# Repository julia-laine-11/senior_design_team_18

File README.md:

# senior_design_team_18

See our teams progress at https://eceseniordesign.com/teams/18?semester=Fall2025

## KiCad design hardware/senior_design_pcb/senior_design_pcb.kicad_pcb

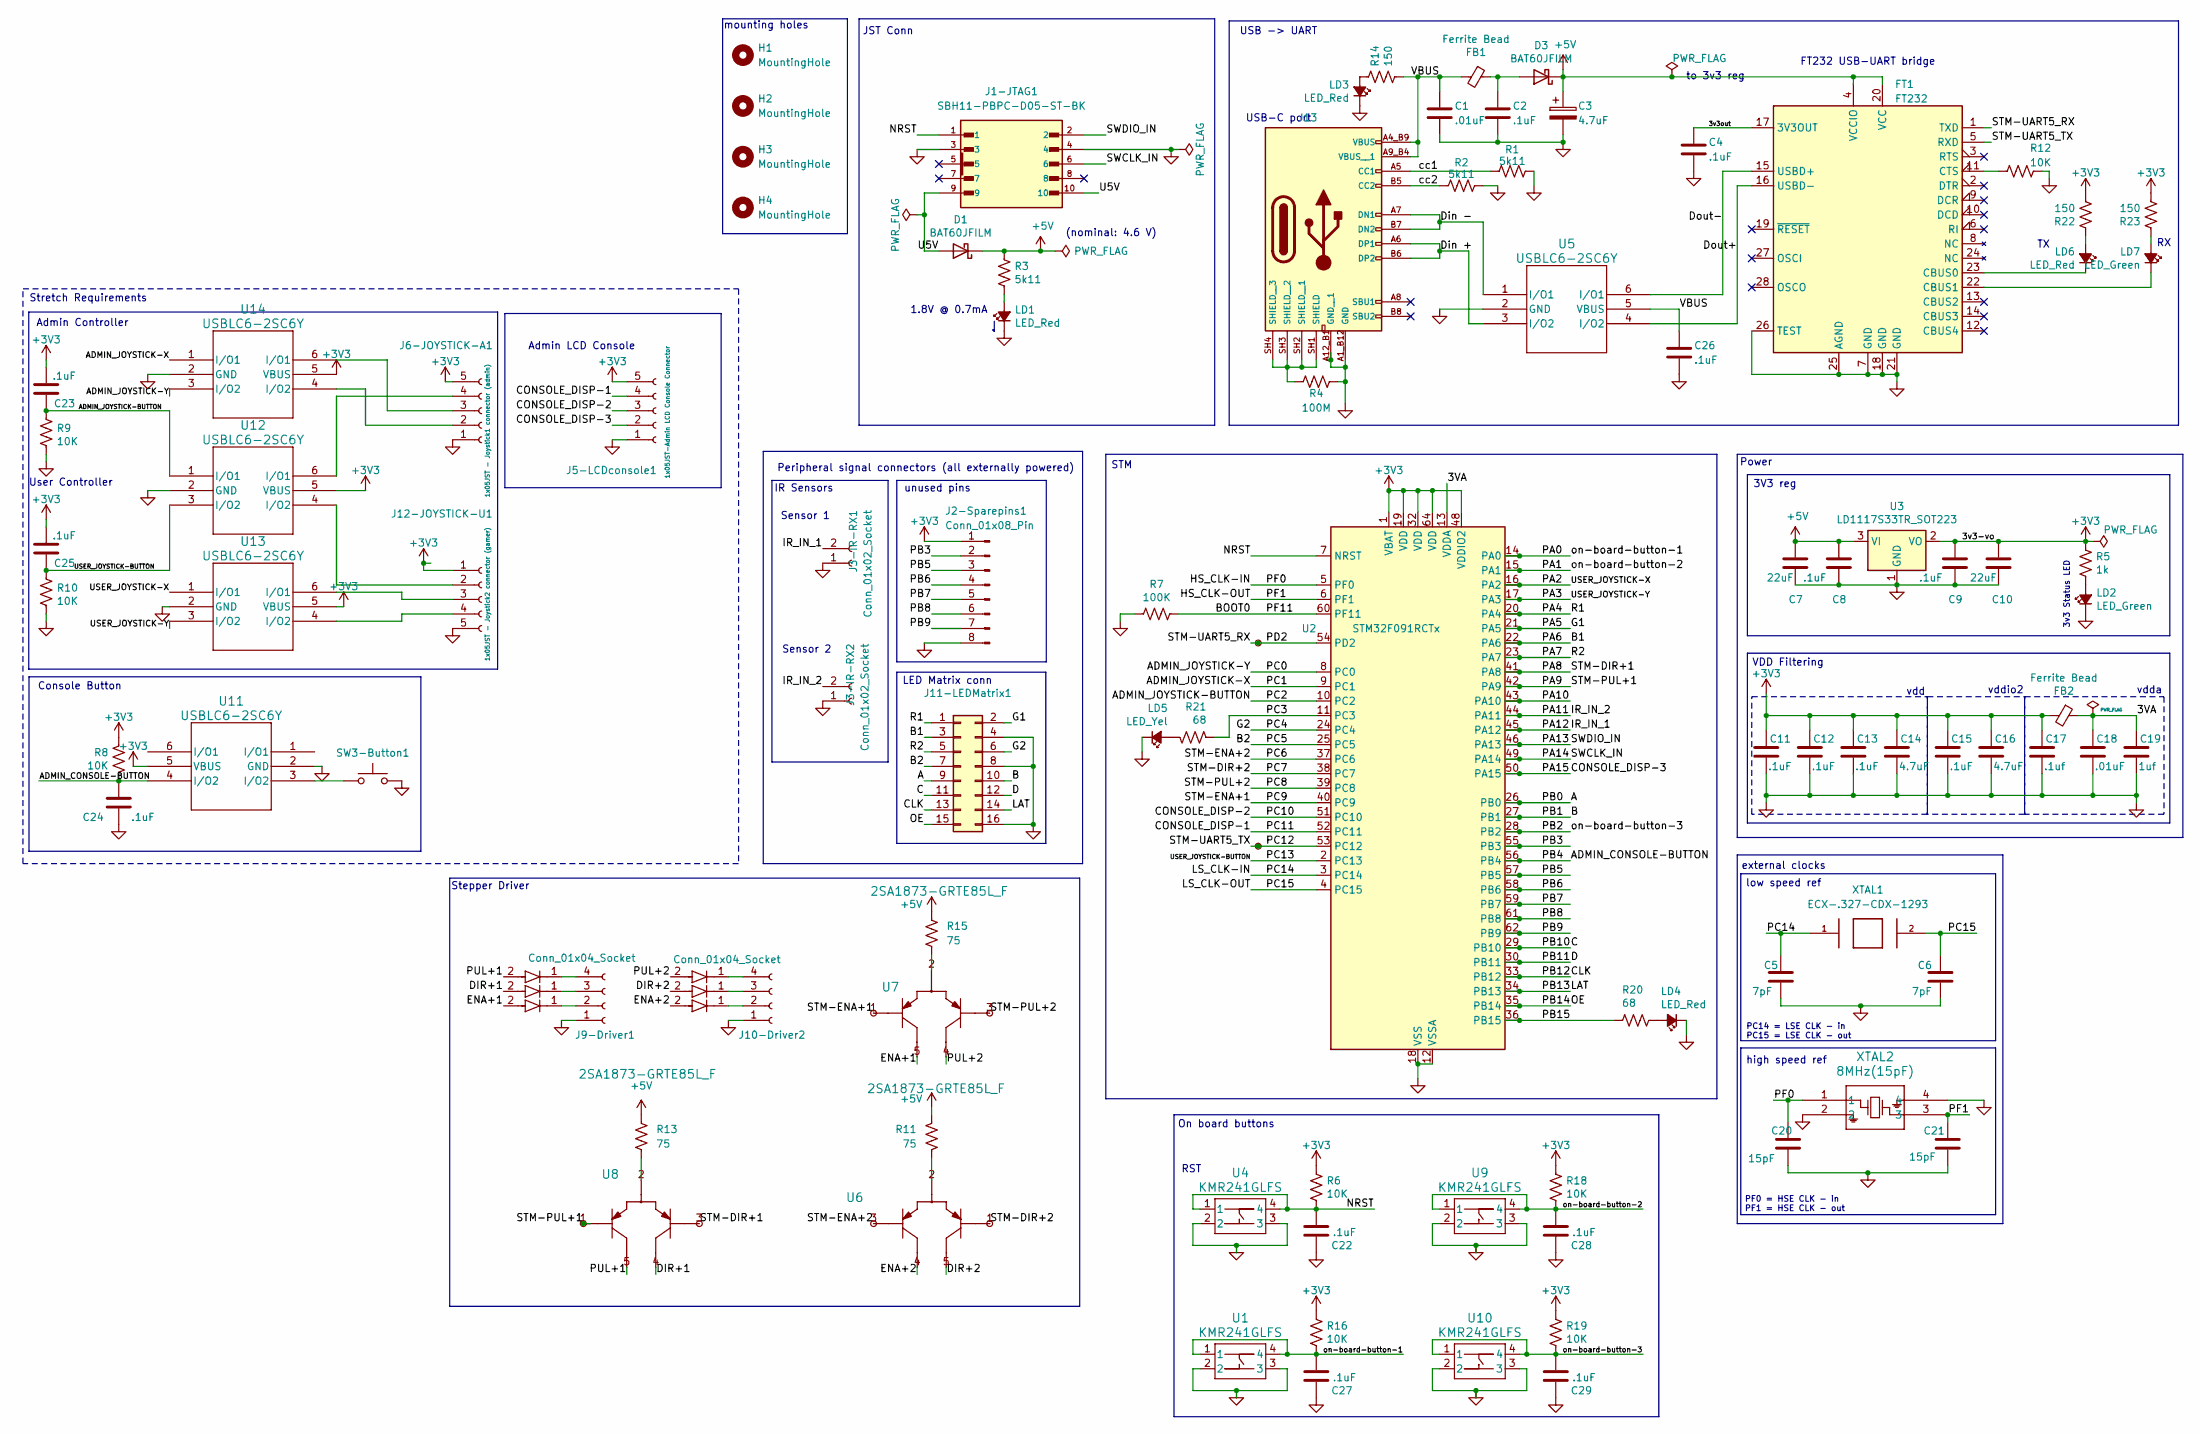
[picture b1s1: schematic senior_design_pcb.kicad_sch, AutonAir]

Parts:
C1, C18: .01uF; C_0805_2012Metric_Pad1.18x1.45mm_HandSolder
C2, C4, C8, C9, C11, C12, C13, C15, C22, C23, C24, C25, C26, C27, C28, C29: .1uF; C_0805_2012Metric_Pad1.18x1.45mm_HandSolder
C3, C14, C16: 4.7uF; C_0805_2012Metric_Pad1.18x1.45mm_HandSolder
C5, C6: 7pF; C_0805_2012Metric_Pad1.18x1.45mm_HandSolder
C7, C10: 22uF; C_0805_2012Metric_Pad1.18x1.45mm_HandSolder
C17: .1uf; C_0805_2012Metric_Pad1.18x1.45mm_HandSolder
C19: 1uf; C_0805_2012Metric_Pad1.18x1.45mm_HandSolder
C20, C21: 15pF; C_0805_2012Metric_Pad1.18x1.45mm_HandSolder
CR1, CR2, CR3, CR4, CR5, CR6: JAN1N4148UR-1; jan1n4148 smd diode-M
D1, D3: BAT60JFILM; D_SOD-323_HandSoldering
FB1, FB2: Ferrite Bead; L_0805_2012Metric_Pad1.05x1.20mm_HandSolder
FT1: FT232; SSOP-28_5.3x10.2mm_P0.65mm
H1, H2, H3, H4: MountingHole; MountingHole_3.2mm_M3
J1-JTAG1: SBH11-PBPC-D05-ST-BK; jtag_conn; PARTREV J
J2-Sparepins1: Conn_01x08_Pin; PinHeader_1x08_P2.54mm_Vertical
J3-IR-RX1, J3-IR-RX2: Conn_01x02_Socket; JST_EH_B2B-EH-A_1x02_P2.50mm_Vertical
J5-LCDconsole1: 1x05JST-Admin LCD Console Connector; JST_EH_B5B-EH-A_1x05_P2.50mm_Vertical
J6-JOYSTICK-A1: 1x05JST - Joystick1 connector (admin); JST_EH_B5B-EH-A_1x05_P2.50mm_Vertical
J9-Driver1, J10-Driver2: Conn_01x04_Socket; JST_EH_B4B-EH-A_1x04_P2.50mm_Vertical
J11-LEDMatrix1: 2x08Rectangle-LED Matrix Connector; jst-02x08 conn
J12-JOYSTICK-U1: 1x05JST - Joystick2 connector (gamer); JST_EH_B5B-EH-A_1x05_P2.50mm_Vertical
J13: UJ20-C-H-C-4-SMT-TR; USB-C-PORT-2; PARTREV 1.0
LD1, LD3, LD4, LD6: LED_Red; LED_0805_2012Metric
LD2, LD7: LED_Green; LED_0805_2012Metric
LD5: LED_Yel; LED_0805_2012Metric
R1, R2, R3: 5k11; R_0805_2012Metric_Pad1.20x1.40mm_HandSolder
R4: 100M; R_0805_2012Metric_Pad1.20x1.40mm_HandSolder
R5: 1k; R_0805_2012Metric_Pad1.20x1.40mm_HandSolder
R6, R8, R9, R10, R12, R16, R18, R19: 10K; R_0805_2012Metric_Pad1.20x1.40mm_HandSolder
R7: 100K; R_0805_2012Metric_Pad1.20x1.40mm_HandSolder
R11, R13, R15: 75; R_0805_2012Metric_Pad1.20x1.40mm_HandSolder
R14, R22, R23: 150; R_0805_2012Metric_Pad1.20x1.40mm_HandSolder
R20, R21: 68; R_0805_2012Metric_Pad1.20x1.40mm_HandSolder
SW3-Button1: 1x02JST-Admin Console button connector; PinHeader_1x02_P2.54mm_Vertical
TP7, TP8, TP9, TP10, TP11, TP12, TP13, TP14: TestPoint_Small; TestPoint_THTPad_D1.0mm_Drill0.5mm
U1, U4, U9, U10: KMR241GLFS; KMR241G-RESET-BUTTON
U2: STM32F091RCTx; LQFP-64_10x10mm_P0.5mm
U3: LD1117S33TR_SOT223; SOT-223-3_TabPin2
U5, U11, U12, U13, U14: USBLC6-2SC6Y; TVS-DIODE-USBLC6-2SC6Y
U6, U7, U8: 2SA1873-GRTE85L_F; TRANS 2PNP-2SA1873
XTAL1: ECX-.327-CDX-1293; 32khz clock - crystal
XTAL2: 8MHz(15pF); ECS-CRYSTAL 8MHZ 8PF SMD

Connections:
+3V3: C9.1, C10.1, C11.1, C12.1, C13.1, C14.1, C15.1, C16.1, C17.1, C23.1, C25.1, FB2.2, J2-Sparepins1.1, J5-LCDconsole1.5, J6-JOYSTICK-A1.5, J12-JOYSTICK-U1.1, R5.1, R6.1, R8.1, R16.1, R18.1, R19.1, R22.2, R23.2, U2.1 (VBAT), U2.19 (VDD), U2.32 (VDD), U2.48 (VDDIO2), U2.64 (VDD), U3.2 (VO), U11.5 (VBUS), U12.5 (VBUS), U13.5 (VBUS), U14.5 (VBUS)
+5V: C3.1, C7.1, C8.1, D1.1 (K), D3.1 (K), FT1.4 (VCCIO), FT1.20 (VCC), R3.1, R11.1, R13.1, R15.1, U3.3 (VI)
/3VA: C18.1, C19.1, FB2.1, U2.13 (VDDA)
/3v3out: C4.1, FT1.17 (3V3OUT)
/A: J11-LEDMatrix1.9, U2.26 (PB0)
/ADMIN_CONSOLE-BUTTON: C24.1, R8.2, U2.56 (PB4), U11.4 (I/O2)
/ADMIN_JOYSTICK-BUTTON: C23.2, R9.1, U2.10 (PC2), U12.1 (I/O1)
/ADMIN_JOYSTICK-X: U2.9 (PC1), U14.1 (I/O1)
/ADMIN_JOYSTICK-Y: U2.8 (PC0), U14.3 (I/O2)
/B: J11-LEDMatrix1.10, U2.27 (PB1)
/B1: J11-LEDMatrix1.3, U2.22 (PA6)
/B2: J11-LEDMatrix1.7, U2.25 (PC5)
/BOOT0: R7.1, U2.60 (PF11)
/C: J11-LEDMatrix1.11, U2.29 (PB10)
/CLK: J11-LEDMatrix1.13, U2.33 (PB12)
/CONSOLE_DISP-1: J5-LCDconsole1.4, U2.52 (PC11)
/CONSOLE_DISP-2: J5-LCDconsole1.3, U2.51 (PC10)
/CONSOLE_DISP-3: J5-LCDconsole1.2, U2.50 (PA15)
/D: J11-LEDMatrix1.12, U2.30 (PB11)
/DIR+1: CR2.2, U8.4
/DIR+2: CR5.2, U6.5
/Din +: J13.A6 (DP1), J13.B6 (DP2), U5.3 (I/O2)
/Din -: J13.A7 (DN1), J13.B7 (DN2), U5.1 (I/O1)
/Dout+: FT1.16 (USBD-), U5.4 (I/O2)
/Dout-: FT1.15 (USBD+), U5.6 (I/O1)
/ENA+1: CR3.2, U7.5
/ENA+2: CR6.2, U6.4
/G1: J11-LEDMatrix1.2, U2.21 (PA5)
/G2: J11-LEDMatrix1.6, U2.24 (PC4)
/HS_CLK-IN: C20.1, U2.5 (PF0), XTAL2.1
/HS_CLK-OUT: C21.1, U2.6 (PF1), XTAL2.3
/IR_IN_1: J3-IR-RX1.2, U2.45 (PA12)
/IR_IN_2: J3-IR-RX2.2, U2.44 (PA11)
/LAT: J11-LEDMatrix1.14, U2.34 (PB13)
/LS_CLK-IN: C5.1, U2.3 (PC14), XTAL1.1
/LS_CLK-OUT: C6.1, U2.4 (PC15), XTAL1.2
/NRST: C22.1, J1-JTAG1.1, R6.2, U2.7 (NRST), U4.1, U4.4
/OE: J11-LEDMatrix1.15, U2.35 (PB14)
/PA0: C27.1, R16.2, U1.1, U1.4, U2.14 (PA0)
/PA1: C28.1, R18.2, U2.15 (PA1), U9.1, U9.4
/PA2: U2.16 (PA2), U13.1 (I/O1)
/PA3: U2.17 (PA3), U13.3 (I/O2)
/PA4: J11-LEDMatrix1.1, U2.20 (PA4)
/PA7: J11-LEDMatrix1.5, U2.23 (PA7)
/PA8: TP12.1, U2.41 (PA8), U8.3
/PA9: TP11.1, U2.42 (PA9), U8.1
/PA10: U2.43 (PA10)
/PA13: J1-JTAG1.2, U2.46 (PA13)
/PA14: J1-JTAG1.6, U2.49 (PA14)
/PB2: C29.1, R19.2, U2.28 (PB2), U10.1, U10.4
/PB3: J2-Sparepins1.2, U2.55 (PB3)
/PB5: J2-Sparepins1.3, U2.57 (PB5)
/PB6: J2-Sparepins1.4, U2.58 (PB6)
/PB7: J2-Sparepins1.5, U2.59 (PB7)
/PB8: J2-Sparepins1.6, U2.61 (PB8)
/PB9: J2-Sparepins1.7, U2.62 (PB9)
/PB15: R20.1, U2.36 (PB15)
/PC3: R21.1, U2.11 (PC3)
/PC6: TP7.1, U2.37 (PC6), U6.3
/PC7: TP8.1, U2.38 (PC7), U6.1
/PC8: TP10.1, U2.39 (PC8), U7.3
/PC9: TP9.1, U2.40 (PC9), U7.1
/PC12: FT1.5 (RXD), TP13.1, U2.53 (PC12)
/PC13: C25.2, R10.1, U2.2 (PC13), U12.3 (I/O2)
/PD2: FT1.1 (TXD), TP14.1, U2.54 (PD2)
/PUL+1: CR1.2, U8.5
/PUL+2: CR4.2, U7.4
/U5V: D1.2 (A), J1-JTAG1.9, J1-JTAG1.10
/VBUS: C1.1, C26.1, FB1.2, J13.A4_B9 (VBUS), J13.A9_B4 (VBUS__1), R14.2, U5.5 (VBUS)
/cc1: J13.A5 (CC1), R1.1
/cc2: J13.B5 (CC2), R2.1
GND: C1.2, C2.2, C3.2, C4.2, C5.2, C6.2, C7.2, C8.2, C9.2, C10.2, C11.2, C12.2, C13.2, C14.2, C15.2, C16.2, C17.2, C18.2, C19.2, C20.2, C21.2, C22.2, C24.2, C26.2, C27.2, C28.2, C29.2, FT1.7 (GND), FT1.18 (GND), FT1.21 (GND), FT1.25 (AGND), FT1.26 (TEST), J1-JTAG1.3, J1-JTAG1.4, J2-Sparepins1.8, J3-IR-RX1.1, J3-IR-RX2.1, J5-LCDconsole1.1, J6-JOYSTICK-A1.1, J9-Driver1.1, J10-Driver2.1, J11-LEDMatrix1.4, J11-LEDMatrix1.8, J11-LEDMatrix1.16, J12-JOYSTICK-U1.5, J13.A1_B12 (GND), J13.A12_B1 (GND__1), LD1.1 (K), LD2.1 (K), LD3.1 (K), LD4.1 (K), LD5.1 (K), R1.2, R2.2, R4.1, R7.2, R9.2, R10.2, R12.2, SW3-Button1.1, U1.2, U1.3, U2.12 (VSSA), U2.18 (VSS), U2.31 (VSS), U2.47 (VSS), U2.63 (VSS), U3.1 (GND), U4.2, U4.3, U5.2 (GND), U9.2, U9.3, U10.2, U10.3, U11.2 (GND), U12.2 (GND), U13.2 (GND), U14.2 (GND), XTAL2.2, XTAL2.4
unnamed: C2.1, D3.2 (A), FB1.1
unnamed: FT1.23 (CBUS0), LD6.1 (K)
unnamed: FT1.22 (CBUS1), LD7.1 (K)
unnamed: FT1.11 (CTS), R12.1
unnamed: J6-JOYSTICK-A1.2, U14.4 (I/O2)
unnamed: J6-JOYSTICK-A1.3, U14.6 (I/O1)
unnamed: J6-JOYSTICK-A1.4, U12.6 (I/O1)
unnamed: CR3.1, J9-Driver1.2
unnamed: CR2.1, J9-Driver1.3
unnamed: CR1.1, J9-Driver1.4
unnamed: CR6.1, J10-Driver2.2
unnamed: CR5.1, J10-Driver2.3
unnamed: CR4.1, J10-Driver2.4
unnamed: J12-JOYSTICK-U1.2, U12.4 (I/O2)
unnamed: J12-JOYSTICK-U1.3, U13.6 (I/O1)
unnamed: J12-JOYSTICK-U1.4, U13.4 (I/O2)
unnamed: J13.SH1 (SHIELD), J13.SH2 (SHIELD__1), J13.SH3 (SHIELD__2), J13.SH4 (SHIELD__3), R4.2
unnamed: LD1.2 (A), R3.2
unnamed: LD2.2 (A), R5.2
unnamed: LD3.2 (A), R14.1
unnamed: LD4.2 (A), R20.2
unnamed: LD5.2 (A), R21.2
unnamed: LD6.2 (A), R22.1
unnamed: LD7.2 (A), R23.1
unnamed: R11.2, U6.2
unnamed: R13.2, U8.2
unnamed: R15.2, U7.2
unnamed: SW3-Button1.2, U11.3 (I/O2)

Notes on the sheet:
On board buttons
Sensor 2
unused pins
JST Conn
USB-C port
Console Button
RST
external clocks
low speed ref
high speed ref
Power
3v3 Status LED
STM
3V3 reg
Admin Controller
Peripheral signal connectors (all externally powered)
vdd
vdda
PF0 = HSE CLK - in PF1 = HSE CLK - out
FT232 USB-UART bridge
vddio2
Stepper Driver
to 3v3 reg
Admin LCD Console
IR Sensors
LED Matrix conn
PC14 = LSE CLK - in PC15 = LSE CLK - out
VDD Filtering
USB -> UART
Stretch Requirements
Sensor 1
1.8V @ 0.7mA
User Controller
mounting holes
(nominal: 4.6 V)

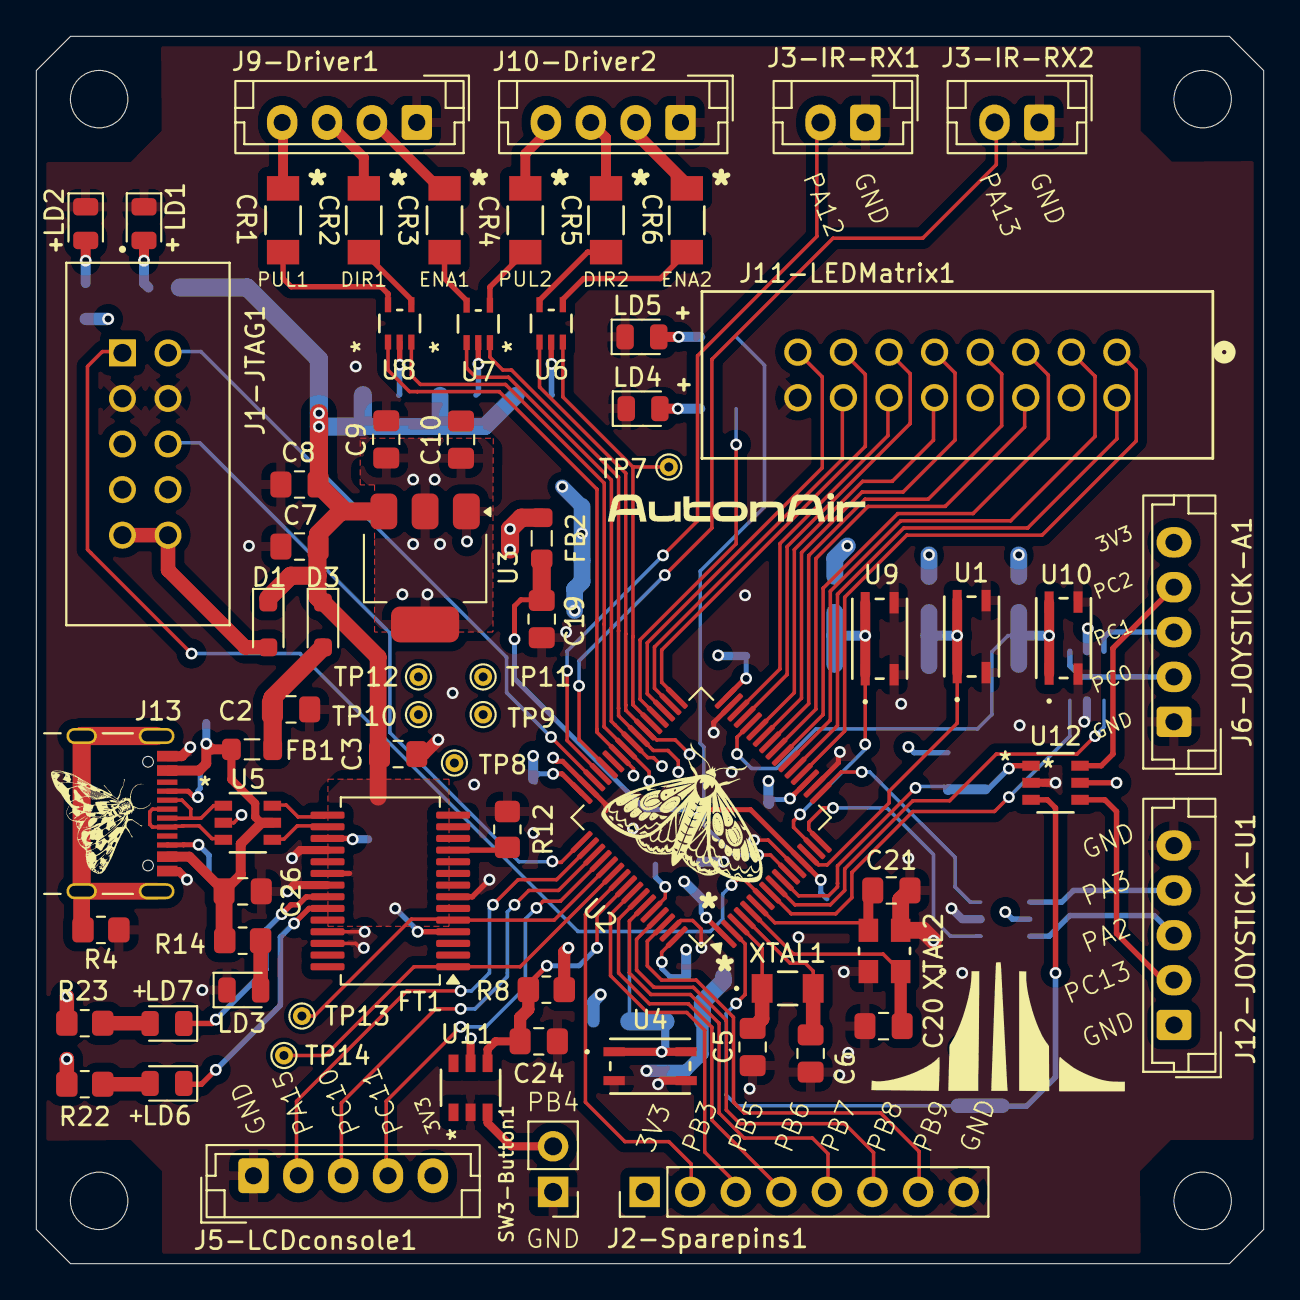
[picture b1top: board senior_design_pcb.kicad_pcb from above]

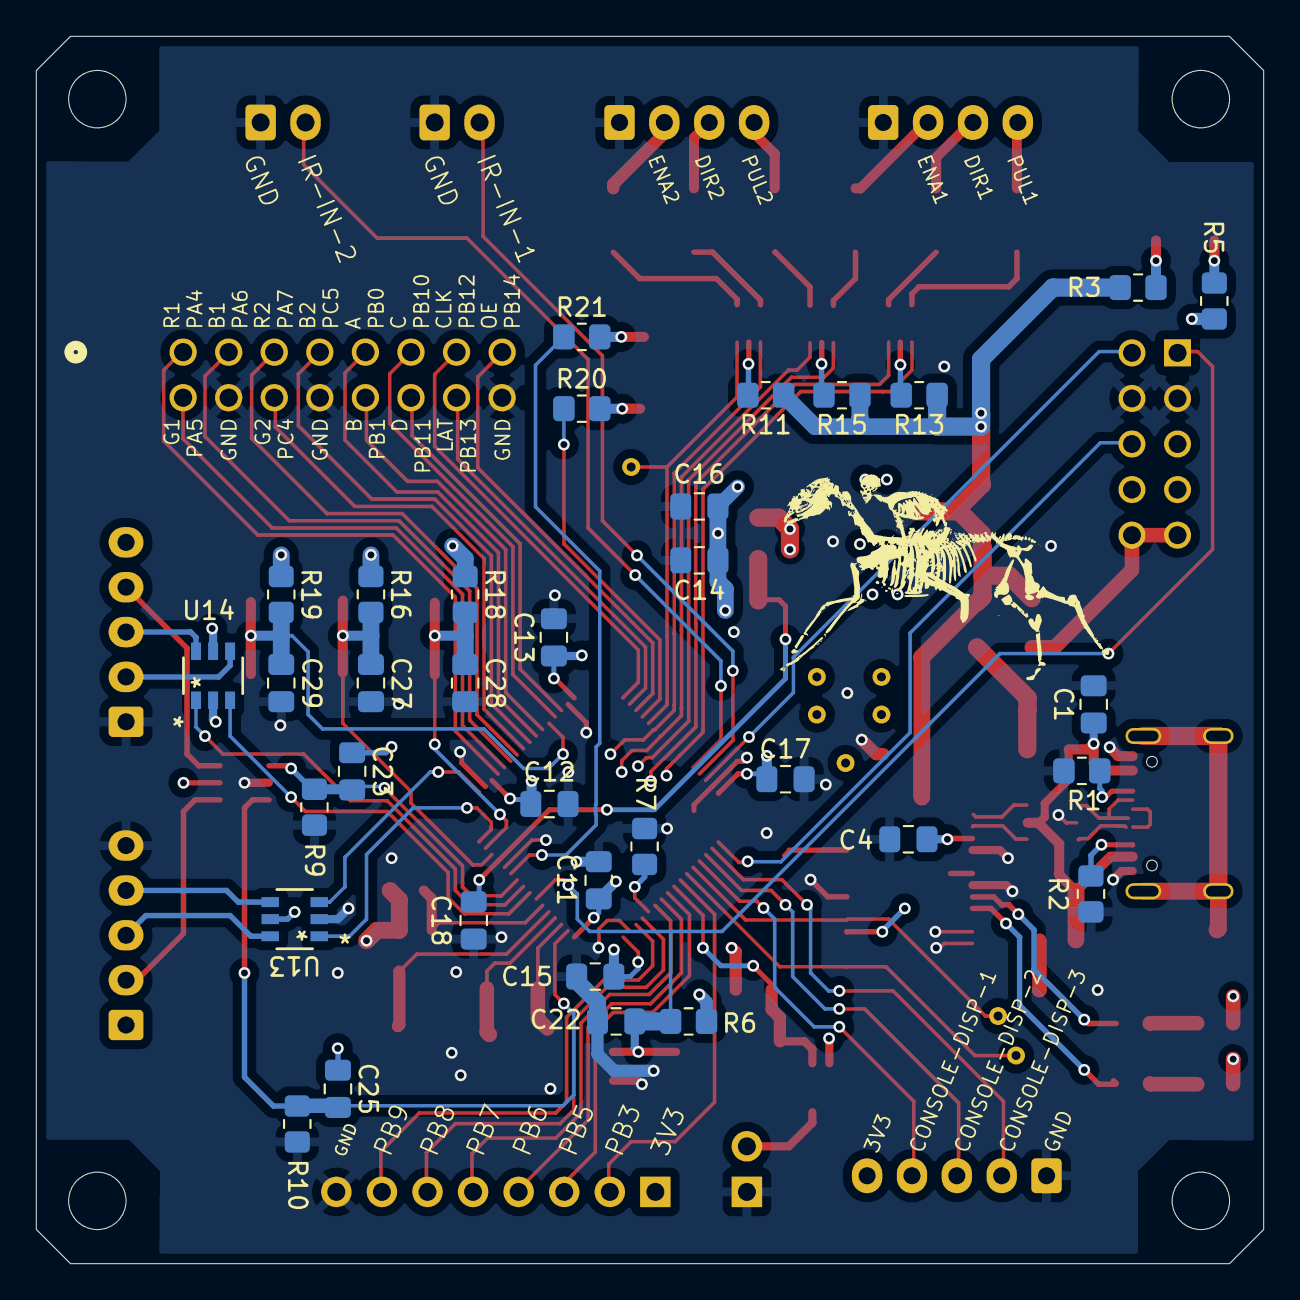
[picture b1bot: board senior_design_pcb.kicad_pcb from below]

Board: 4 copper layers, 68.4 x 68.4 mm, 109 parts (34 on the bottom side), 99 nets.

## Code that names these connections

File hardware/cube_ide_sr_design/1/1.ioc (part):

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Mcu.Name=STM32F091R(B-C)Tx
Mcu.Package=LQFP64
Mcu.UserName=STM32F091RCTx
PA13.GPIOParameters=GPIO_Label
PA13.GPIO_Label=JST-SWDIO_IN
PA13.Mode=Serial_Wire
PA13.Signal=SYS_SWDIO
PA14.GPIOParameters=GPIO_Label
PA14.GPIO_Label=JST-SWCLK_IN
PA14.Mode=Serial_Wire
PA14.Signal=SYS_SWCLK
PA2.GPIOParameters=GPIO_Label
PA2.GPIO_Label=LED-OE
PA2.Signal=GPIO_Output
PA3.GPIOParameters=GPIO_Label
PA3.GPIO_Label=LED-LAT
PA3.Signal=GPIO_Output
PA4.GPIOParameters=GPIO_Label
PA4.GPIO_Label=LED-CLK
PA4.Signal=GPIO_Output
PA5.GPIOParameters=GPIO_Label
PA5.GPIO_Label=LED-D
PA5.Signal=GPIO_Output
PA6.GPIOParameters=GPIO_Label
PA6.GPIO_Label=LED-C
PA6.Signal=GPIO_Output
PA7.GPIOParameters=GPIO_Label
PA7.GPIO_Label=LED-B
PA7.Signal=GPIO_Output
PA8.GPIOParameters=GPIO_Label
PA8.GPIO_Label=IR_IN_2
PA8.Signal=GPIO_Input
PA9.GPIOParameters=GPIO_Label
PA9.GPIO_Label=IR_IN_1
PA9.Signal=GPIO_Input
PB0.GPIOParameters=GPIO_Label
PB0.GPIO_Label=LED-G2
PB0.Signal=GPIO_Output
PB1.GPIOParameters=GPIO_Label
PB1.GPIO_Label=LED-R2
PB1.Signal=GPIO_Output
PB10.GPIOParameters=GPIO_Label
PB10.GPIO_Label=LED-G1
PB10.Signal=GPIO_Output
PB11.GPIOParameters=GPIO_Label
PB11.GPIO_Label=LED-R1
PB11.Signal=GPIO_Output
PB12.GPIOParameters=GPIO_Label
PB12.GPIO_Label=Step2_out3
PB12.Signal=GPIO_Output
PB13.GPIOParameters=GPIO_Label
PB13.GPIO_Label=Step2_out2
PB13.Signal=GPIO_Output
PB14.GPIOParameters=GPIO_Label
PB14.GPIO_Label=Step2_out1
PB14.Signal=GPIO_Output
PB15.GPIOParameters=GPIO_Label
PB15.GPIO_Label=Step2_input
PB15.Signal=GPIO_Input
PB2.GPIOParameters=GPIO_Label
PB2.GPIO_Label=LED-B1
PB2.Signal=GPIO_Output
PB4.GPIOParameters=GPIO_Label
PB4.GPIO_Label=ADMIN-CONSOLE_BUTTON
PB4.Signal=GPIO_Output
PB5.GPIOParameters=GPIO_Label
PB5.GPIO_Label=ADMIN-JOYSTICK_BUTTON
PB5.Signal=GPIO_Output
PB6.GPIOParameters=GPIO_Label
PB6.GPIO_Label=ADMIN-JOYSTICK_Y
PB6.Signal=GPIO_Output
PB7.GPIOParameters=GPIO_Label
PB7.GPIO_Label=ADMIN-JOYSTICK_X
PB7.Signal=GPIO_Output
PB8.GPIOParameters=GPIO_Label
PB8.GPIO_Label=ADMIN-CONSOLE_DISP2
PB8.Signal=GPIO_Output
PB9.GPIOParameters=GPIO_Label
PB9.GPIO_Label=ADMIN-CONSOLE_DISP1
PB9.Signal=GPIO_Output
PC0.GPIOParameters=GPIO_Label
PC0.GPIO_Label=CONTROLLER_X
PC0.Mode=IN10
PC0.Signal=ADC_IN10
PC1.GPIOParameters=GPIO_Label
PC1.GPIO_Label=CONTROLLER Y
PC1.Mode=IN11
PC1.Signal=ADC_IN11
PC12.GPIOParameters=GPIO_Label
PC12.GPIO_Label=USB-USART5_TX
PC12.Mode=Asynchronous
PC12.Signal=USART5_TX
PC14OSC32_IN.GPIOParameters=GPIO_Label
PC14OSC32_IN.GPIO_Label=LOW_SPEED-IN
PC14OSC32_IN.Mode=LSE-External-Oscillator
PC14OSC32_IN.Signal=RCC_OSC32_IN
PC15OSC32_OUT.GPIOParameters=GPIO_Label
PC15OSC32_OUT.GPIO_Label=LOW_SPEED-OUT
PC15OSC32_OUT.Mode=LSE-External-Oscillator
PC15OSC32_OUT.Signal=RCC_OSC32_OUT
PC4.GPIOParameters=GPIO_Label
PC4.GPIO_Label=LED-A
PC4.Signal=GPIO_Output
PC5.GPIOParameters=GPIO_Label
PC5.GPIO_Label=LED-B2
PC5.Signal=GPIO_Output
PC6.GPIOParameters=GPIO_Label
PC6.GPIO_Label=Step1_out3
PC6.Signal=GPIO_Output
PC7.GPIOParameters=GPIO_Label
PC7.GPIO_Label=Step1_out2
PC7.Signal=GPIO_Output
PC8.GPIOParameters=GPIO_Label
PC8.GPIO_Label=Step1_out1
PC8.Signal=GPIO_Output
PC9.GPIOParameters=GPIO_Label
PC9.GPIO_Label=Step1_input
PC9.Signal=GPIO_Input
PD2.GPIOParameters=GPIO_Label
PD2.GPIO_Label=USB-USART5_RX
PD2.Mode=Asynchronous
PD2.Signal=USART5_RX
PF0-OSC_IN.GPIOParameters=GPIO_Label
PF0-OSC_IN.GPIO_Label=HIGH_SPEED-IN
PF0-OSC_IN.Mode=HSE-External-Oscillator
PF0-OSC_IN.Signal=RCC_OSC_IN
PF1-OSC_OUT.GPIOParameters=GPIO_Label
PF1-OSC_OUT.GPIO_Label=HIGH_SPEED-OUT
PF1-OSC_OUT.Mode=HSE-External-Oscillator
PF1-OSC_OUT.Signal=RCC_OSC_OUT
PF11BOOT0.GPIOParameters=GPIO_Label
PF11BOOT0.GPIO_Label=ADMIN-CONSOLE_DISP3
PF11BOOT0.Signal=GPIO_Output
RCC.SYSCLKFreq_VALUE=8000000
board=custom

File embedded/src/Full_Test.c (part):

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// //===========================================================================
// // TRUE HUB75 MATRIX SCAN (64-Pin Layout)
// //===========================================================================
// // Data: PA4(R1), PA5(G1), PA6(B1), PA7(R2), PC4(G2), PC5(B2)
// // Control: PB12(CLK), PB13(LAT), PB14(OE)
// // Address: PB0(A), PB1(B), PB10(C), PB11(D)

// static inline void Matrix_Scan(uint8_t row) {
//     // 1. SHIFT DATA IN BACKGROUND
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//         GPIOA->BSRR = ((p & 0xF) << 4) | ((~(p & 0xF) & 0xF) << 20);
//         GPIOC->BSRR = ((p & 0x30)) | ((~(p & 0x30) & 0x30) << 16);

//         // Clock Pulse (PB12)
//         GPIOB->BSRR = (1U << 12); 
//         GPIOB->BRR  = (1U << 12); 
//     }

//     // 2. BLANK SCREEN: OE HIGH (PB14)
//     GPIOB->BSRR = (1U << 14); 

//     // 3. LATCH DATA: LAT HIGH then LOW (PB13)
//     GPIOB->BSRR = (1U << 13);
//     for(volatile int i = 0; i < 2; i++); 
//     GPIOB->BRR  = (1U << 13);

//     // 4. UPDATE ADDRESS: A:PB0, B:PB1, C:PB10, D:PB11
//     uint32_t b_set = 0;
//     if (row & 0x01) b_set |= (1U << 0);
//     if (row & 0x02) b_set |= (1U << 1);
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//     GPIOB->BRR = (1U << 0) | (1U << 1) | (1U << 10) | (1U << 11);
//     GPIOB->BSRR = b_set;

//     // 5. DISPLAY ENABLE: OE LOW (PB14)
//     GPIOB->BRR = (1U << 14);
    
//     // 6. ROW DWELL TIME (Brightness)
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// }

// //===========================================================================
// // ADC (Joystick VRY -> PC0)
// //===========================================================================

// void init_adc(void) {
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// //===========================================================================

// void init_controls(void) {
//     // PC2 Input (UI Select)
//     GPIOC->MODER &= ~(GPIO_MODER_MODER2);
//     GPIOC->PUPDR &= ~(GPIO_PUPDR_PUPDR2);
//     GPIOC->PUPDR |= (GPIO_PUPDR_PUPDR2_0);
// }

// void init_sensors(void) {
//     // PA11 (Red), PA12 (Blue)
//     GPIOA->MODER &= ~(GPIO_MODER_MODER11 | GPIO_MODER_MODER12);
//     GPIOA->PUPDR &= ~(GPIO_PUPDR_PUPDR11 | GPIO_PUPDR_PUPDR12);
//     GPIOA->PUPDR |= (GPIO_PUPDR_PUPDR11_0 | GPIO_PUPDR_PUPDR12_0); // Pull-ups
// }

// void init_matrix_gpio(void) {
//     // DATA PA4-7
//     GPIOA->MODER &= ~(0xFF00);
//     GPIOA->MODER |= 0x5500;
    
//     // DATA PC4-5
//     GPIOC->MODER &= ~(0xF00);
//     GPIOC->MODER |= 0x500;

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// void init_uart(void) {
//     RCC->APB1ENR |= RCC_APB1ENR_USART5EN; 

//     // Setup PD2 as RX (Alternate Function 2)
//     GPIOD->MODER &= ~GPIO_MODER_MODER2;
//     GPIOD->MODER |= GPIO_MODER_MODER2_1;        
//     GPIOD->AFR[0] &= ~(0xF << (2 * 4));         
//     GPIOD->AFR[0] |= (2 << (2 * 4));            

//     // Setup PC12 as TX (Alternate Function 2)
//     GPIOC->MODER &= ~GPIO_MODER_MODER12;
//     GPIOC->MODER |= GPIO_MODER_MODER12_1;       
//     GPIOC->AFR[1] &= ~(0xF << ((12 - 8) * 4));  
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//     RCC->APB2ENR |= RCC_APB2ENR_TIM1EN;
//     RCC->APB1ENR |= RCC_APB1ENR_TIM3EN;
    
//     // Motor A: PA8 (DIR), PC9 (ENA), PA9 (PUL)
//     GPIOA->MODER &= ~((3 << 16) | (3 << 18));
//     GPIOA->MODER |= (1 << 16) | (2 << 18); 
//     GPIOA->AFR[1] |= (2 << 4);     
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//     GPIOA->BSRR = (1 << 8); // DIR High
//     GPIOC->BRR  = (1 << 9); // ENA Low (Enabled)

//     // Motor B: PC7 (DIR), PC6 (ENA), PC8 (PUL)
//     GPIOC->MODER &= ~((3 << 12) | (3 << 14) | (3 << 16));
//     GPIOC->MODER |= (1 << 12) | (1 << 14) | (2 << 16);
//     GPIOC->AFR[1] &= ~(0xF << 0);  
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
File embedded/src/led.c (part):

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
// // Pin Locations
// /*
// R1  PC0
// G1  PC1
// B1  PC2
// R2  PC3
// B2  PC4
// G2  PC5
// A   PC6
// B   PC7
// C   PC8
// D   PC9
// OE  PC10
// LAT PC11
// CLK PC13
// */

// //Includes
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// // --- Function Definitions ---

// /**
//  * @brief Initializes GPIOC pins PC0-PC12 for matrix control.
//  */
// void init_matrix_gpio(void)
// {
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//         uint8_t rgb1 = packed_color & 0x07;        // Top row color (RBG)
//         uint8_t rgb2 = (packed_color >> 3) & 0x07; // Bottom row color (RBG)
//         uint32_t rgb_bits_set = 0, rgb_bits_reset = 0;
//         // Top Row (R1=PC0, B1=PC1, G1=PC2)
//         if (rgb1 & 1) rgb_bits_set |= (1U << 0); else rgb_bits_reset |= (1U << 0); // R1
//         if (rgb1 & 2) rgb_bits_set |= (1U << 1); else rgb_bits_reset |= (1U << 1); // B1
//         if (rgb1 & 4) rgb_bits_set |= (1U << 2); else rgb_bits_reset |= (1U << 2); // G1
//         // Bottom Row (R2=PC3, B2=PC4, G2=PC5)
//         if (rgb2 & 1) rgb_bits_set |= (1U << 3); else rgb_bits_reset |= (1U << 3); // R2
//         if (rgb2 & 2) rgb_bits_set |= (1U << 4); else rgb_bits_reset |= (1U << 4); // B2
//         if (rgb2 & 4) rgb_bits_set |= (1U << 5); else rgb_bits_reset |= (1U << 5); // G2
//         // Set/Reset all 6 RGB lines
//         GPIOC->BSRR = rgb_bits_set | (rgb_bits_reset << 16);
//         // Pulse Clock (CLK = PC10)
        
//         GPIOC->BSRR = (1U << 13); 
//         nano_wait(5000);
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
//     GPIOC->BSRR = (1U << 11); // OE High

//     // 4. Pulse Latch (LAT = PC11)
//     GPIOC->BSRR = (1U << 10); 
//     nano_wait(5000);
//     GPIOC->BRR = (1U << 10);
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
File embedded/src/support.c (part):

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
// void setup_dac(void) {
//     RCC->AHBENR |= RCC_AHBENR_GPIOAEN; // Enable GPIOA
//     GPIOA->MODER |= (3 << (4 * 2)); // Set PA4 to analog mode
//     RCC->APB1ENR |= RCC_APB1ENR_DACEN; // Enable DAC clock
//     DAC->CR &= ~DAC_CR_EN1; // Ensure DAC is off
//     DAC->CR &= ~DAC_CR_TEN1; // Disable trigger
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//     RCC -> AHBENR |= RCC_AHBENR_GPIOAEN; 
//     RCC -> AHBENR |= RCC_AHBENR_GPIOCEN;

//     GPIOA -> MODER |= 0x3C; //1100 -> 12 -> C pa1 and 2
 
//     RCC->APB2ENR |= RCC_APB2ENR_ADC1EN; 

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
//     if     (read_adc_channel1() < b1 && read_adc_channel1() > b0) {
//         // GPIOB -> BRR  = 0x1F00;
//         // GPIOB -> BSRR = 0x100;  //PA8
//         thrust_side = a;
//     }
 
//     else if(read_adc_channel1() < b2 && read_adc_channel1() > b1) {
//         // GPIOB -> BRR  = 0x1F00;
//         // GPIOB -> BSRR = 0x200;  //PA9
//         thrust_side = b;
//     }
 
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 
//     else if(read_adc_channel1() < b4 && read_adc_channel1() > b3) {
//         // GPIOB -> BRR  = 0x1F00;
//         // GPIOB -> BSRR = 0x800;  //PA11
//         thrust_side = d;
//     }
 
//     else if(read_adc_channel1() < b5 && read_adc_channel1() > b4) {     
//         // GPIOB -> BRR  = 0x1F00;
//         // GPIOB -> BSRR = 0x1000; //PA12
//         thrust_side = e;
//     }
// ///////////////////////////////////////////////////////////////////////////////////
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
//     if(read_adc_channel2() < v1 && read_adc_channel2() > v0) {
//         // GPIOC -> BRR  = 0x7C; //reset
//         // GPIOC -> BSRR = 0x4;  //Pc2
//         thrust_down = d0;
//     }

//     else if(read_adc_channel2() < v2 && read_adc_channel2() > v1) {
//         // GPIOC -> BRR  = 0x7C; //reset
//         // GPIOC -> BSRR = 0x4;  //Pc2
//         // GPIOC -> BSRR = 0x8;  //Pc3
//         thrust_down = d1;
//     }

//     else if(read_adc_channel2() < v3 && read_adc_channel2() > v2) {
//         // GPIOC -> BRR  = 0x7C;  //reset
//         // GPIOC -> BSRR = 0x4;   //Pc2
//         // GPIOC -> BSRR = 0x8;   //Pc3
//         // GPIOC -> BSRR = 0x10;  //Pc4
//         thrust_down = d2;
//     }

//     else if(read_adc_channel2() < v4 && read_adc_channel2() > v3) {
//         // GPIOC -> BRR  = 0x7C;  //reset
//         // GPIOC -> BSRR = 0x4;   //Pc2
//         // GPIOC -> BSRR = 0x8;   //Pc3
//         // GPIOC -> BSRR = 0x10;  //Pc4
//         // GPIOC -> BSRR = 0x20;  //Pc5
//         thrust_down = d3;

//     }
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//     RCC->APB2ENR |= RCC_APB2ENR_SPI1EN;
//     RCC->AHBENR |= RCC_AHBENR_GPIOAEN;

//     // configure PA15, PA5, PA7
//     GPIOA->MODER &= ~(GPIO_MODER_MODER15 | GPIO_MODER_MODER5 | GPIO_MODER_MODER7);
//     GPIOA->MODER |= (GPIO_MODER_MODER15_1 | GPIO_MODER_MODER5_1 | GPIO_MODER_MODER7_1);

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
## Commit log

2025-09-24 flow chart
    made a flow chart to organize what the PCB needed. I'm currently working on the project proposal and it asks for this :)
2025-09-24 updated chart
2025-09-25 created folders
2025-09-30 added notes from manager meeting
2025-09-30 Inital Object Detection Code
2025-10-02 Add OpenCV model for air hockey puck tracking with interactive sliders
2025-10-14 began schematic
    made a subsheet with components on it. referencing ece362 dev board and my own work. basic stuff so far for just powering and programming the stm
2025-10-14 pushing for the night
    minor updates including adding more words and realigning things
2025-10-14 ok actually pushing for the night
    added usbc receptacle and labeled what would go where
2025-10-21 uart usb work
    added filtering
    added ft232 chip
    added labels
2025-10-22 small progress on usbc
2025-10-22 Moved stuff
2025-10-23 Made poor vison changes
2025-10-27 made some finishing touches to FT232
    removed questionable resistors
    confirmed no CBUS
    confirmed no external osc
    setup bus power
2025-10-27 Added CubeIDE files
    shows pinout. to see the current setup, launch it and view the .ioc file
2025-10-27 Overall formatting (kicad and CubeIDE)
    E96 values
    Labels
    Pin editing (accidentally used BOOT0)
2025-10-28 small tweaks
    added connectors
    added shapes
    added button
    moved shapes
    made bigger sheet
2025-10-28 made it look nice
2025-10-30 moved some stuff
2025-11-02 design rules added
2025-11-03 messed up the ADC for the controller pins so changed those
2025-11-04 vdd caps edited
    apparently 362 gaslight us and they dont have the ones we need so i added more :(
2025-11-06 Add interactive hockey puck tracker and camera test script
    - Implemented `puck_tracker_interactive.py` for real-time tracking of a hockey puck with adjustable boundaries, color selection, and trajectory prediction.
    - Added a GUI for user interaction and configuration of tracking parameters.
    - Created `test_camera.py` to test available camera indices and validate camera settings, including resolution and FPS.
2025-11-07 Add initial implementation of hockey puck and mallet tracking system with robot control framework
2025-11-10 fixed connectors
    apparently things need power so I added pins for that
2025-12-09 annotated. fixed 3v->5v for IR sensors
2025-12-15 added comments
2026-01-18 added pcb, removed schematic level
2026-01-19 organized components
    added labels
    grouped
2026-01-19 edited layout
    made it more finalized, some changes needed still.
2026-01-20 cleaned it up
    added comments and added squares.
    reorganized into more precise rectangles
    marked extra requirements
2026-01-20 Fix path to KiCAD project in README
2026-01-27 test
2026-01-27 added unused pin header
2026-01-27 added kicad library
2026-01-28 added a lot of comments for clarity
2026-01-28 more comments <3
2026-01-28 edited schematic pinouts
    added test points
    edited pinouts for easier traces
    added header
    added comments
    +notes from class today & what to change
2026-02-03 decoupling caps and diffe pair
2026-02-03 decoupling - usbc + ft232
2026-02-05 added mosfets for driver control
    added resistors
    added labels
    added comments
2026-02-11 updated pcb
    shrunk edge cuts
    added footprints for pnp
    added new symbol for pnp
    reorganized stm pinout for easier routing
    moved connectors
2026-02-12 embedded folder created and code added
2026-02-14 routed more traces
    just routed some more. oh and i also added an LED bc there was a pin i forgot we werent using anymore so like why not make it an on board led yk.
2026-02-16 cleaned up
2026-02-17 reorganized
    updated + finished reorg
    added footprints
    added 2x8 jtag 3d file
2026-02-17 led matrix updates
2026-02-17 merge
2026-02-17 oled display support added 1
2026-02-18 main with working joystick start and oled display
2026-02-18 new tracker for Linux sysytem
2026-02-23 Update README with team progress link
    Removed outdated KiCAD project access instructions and added a link to the team's progress.
2026-02-24 3v3 exclusion zones
    decoupling caps had connection to 3v3 straight to the pin. should route through the cap not just be attached. adding exclusion zones to vias and routing 3v3 to the cap pad
2026-02-27 motor code working slightly, enable logic not working
2026-02-27 Added color tuning, and Puck and Mallet specifc ROIs and better lost puck detection
2026-03-05 updated pcb
    changes:
    -all suggested from Setsuna & Shivam & presentation feedback
    -removed r4 and r17
    -kept multiple net names (following PCB Design Techniques - Spring 2025 from brightspace)
    -fixed XTAL1 missing connection
    -removed PWR_FLAG on GND
2026-03-06 final gerber
    ordered pcb
2026-03-11 python based motor control
2026-03-11 Motor Testing
2026-03-11 separate motor control from script
2026-03-11 Updated to two motors
2026-03-11 updated two motor drive
2026-03-25 in progress code for basic camera based motor control
2026-03-30 added to library
2026-03-31 manual diffy motor control
2026-03-31 fix inverted controls, red zone full stop, 4 separate red zone sliders
2026-03-31 linux port support
2026-03-31 full-screen red zone sliders, 90deg CW display rotation, home position G key
2026-03-31 fix homing direction: inverse 90deg rotation from camera to command space
2026-04-01 velocity-based drive, linear homing, 65% motor cap, directional red zone escape
2026-04-01 fix camera crash on Linux: safer VideoCapture init and in-loop error handling
2026-04-01 emergency stop on any crash: try/finally always sends motor stop
2026-04-01 fix: cap variable name collision crashed camera on move, add Linux deps
2026-04-01 fix red zone boundary: block correct command axis per camera wall (90deg rotation)
2026-04-01 FULL AUTO DEFENSE?
2026-04-01 fix: update defensive mode
2026-04-02 Code updates
2026-04-07 intermediary changed
2026-04-14 Added save config and updated defense logic
2026-04-15 Testing Late Night We Grind about to go on a Canes run
2026-04-15 flix y axis
2026-04-15 flip y in auto mode
2026-04-15 edit drive
2026-04-15 add json to gitignore
2026-04-15 Just need to commit
2026-04-15 working IR sensors
2026-04-15 Flip y
2026-04-15 fix auto drive
2026-04-15 fix auto driving
2026-04-15 fix auto this time?
2026-04-15 Re org directions
2026-04-15 stil trying to drive it correctly...
2026-04-15 move fixes
2026-04-15 auto fixes
2026-04-15 IDK even more
2026-04-15 maybe fixed...
2026-04-15 It do be 12:18
2026-04-15 updated embedded code but not tested
2026-04-16 Upload FIX
2026-04-16 setup for motor testing
2026-04-22 pre stretch optimization checkpoint
2026-04-22 remaining changes
2026-04-22 chilling code
2026-04-22 upate weVibin
2026-04-22 less bounces
2026-04-22 New scoreing screen
2026-04-22 removed deacc damp
2026-04-22 anim update
2026-04-22 Stop stutter and add clear logic
2026-04-22 error message
2026-04-22 fix crash
2026-04-26 PreSpark
2026-04-26 fix movement and add mallet slider
2026-04-26 current files split into header files and subfunc c files
2026-04-27 vibezilla: lethal edition
2026-04-27 make mallet orange
2026-04-29 fix: update defensive mode again
2026-04-29 camera data
2026-04-29 fix: better camera fps
2026-04-30 reanme files
2026-04-30 fix stopping issue
2026-05-01 fix movement and add window setting
2026-05-01 fix Mask window
2026-05-01 fix clearning mode
